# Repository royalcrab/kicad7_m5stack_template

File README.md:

# KiCad7-M5Stack-Template for KiCad7

- [Original](https://github.com/botanicfields/KiCad-Template-M5Stack)

A PCB template of modules of M5Stack with footprints for KiCad.
This is a modified version for KiCad7.

## for KiCad 6
https://github.com/botanicfields/KiCad6-Environment

## for KiCad 5
- Manufacture with a thickness of 1.0 mm.
- M-BUS pin numbers match pin headers and pin sockets in the KiCad library.
- The template has a notch, but it may be actually needed only for the M5Stack controller board.

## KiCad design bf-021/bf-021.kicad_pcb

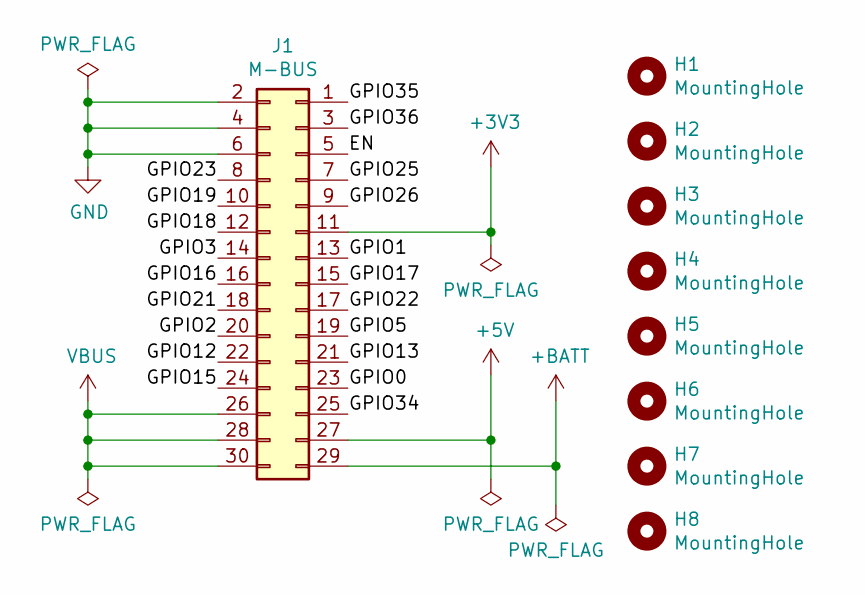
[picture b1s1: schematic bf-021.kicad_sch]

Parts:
H1, H2, H3, H4: MountingHole; BF@MountingHole_3.2mm_M3
H5, H6, H7, H8: MountingHole; BF@MountingHole_2.2mm_M2
J1: M-BUS; BF@M5Stack_MBUS

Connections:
+3V3: J1.11
+5V: J1.27
+BATT: J1.29
/EN: J1.5
/GPIO0: J1.23
/GPIO1: J1.13
/GPIO2: J1.20
/GPIO3: J1.14
/GPIO5: J1.19
/GPIO12: J1.22
/GPIO13: J1.21
/GPIO15: J1.24
/GPIO16: J1.16
/GPIO17: J1.15
/GPIO18: J1.12
/GPIO19: J1.10
/GPIO21: J1.18
/GPIO22: J1.17
/GPIO23: J1.8
/GPIO25: J1.7
/GPIO26: J1.9
/GPIO34: J1.25
/GPIO35: J1.1
/GPIO36: J1.3
GND: J1.2, J1.4, J1.6
VBUS: J1.26, J1.28, J1.30

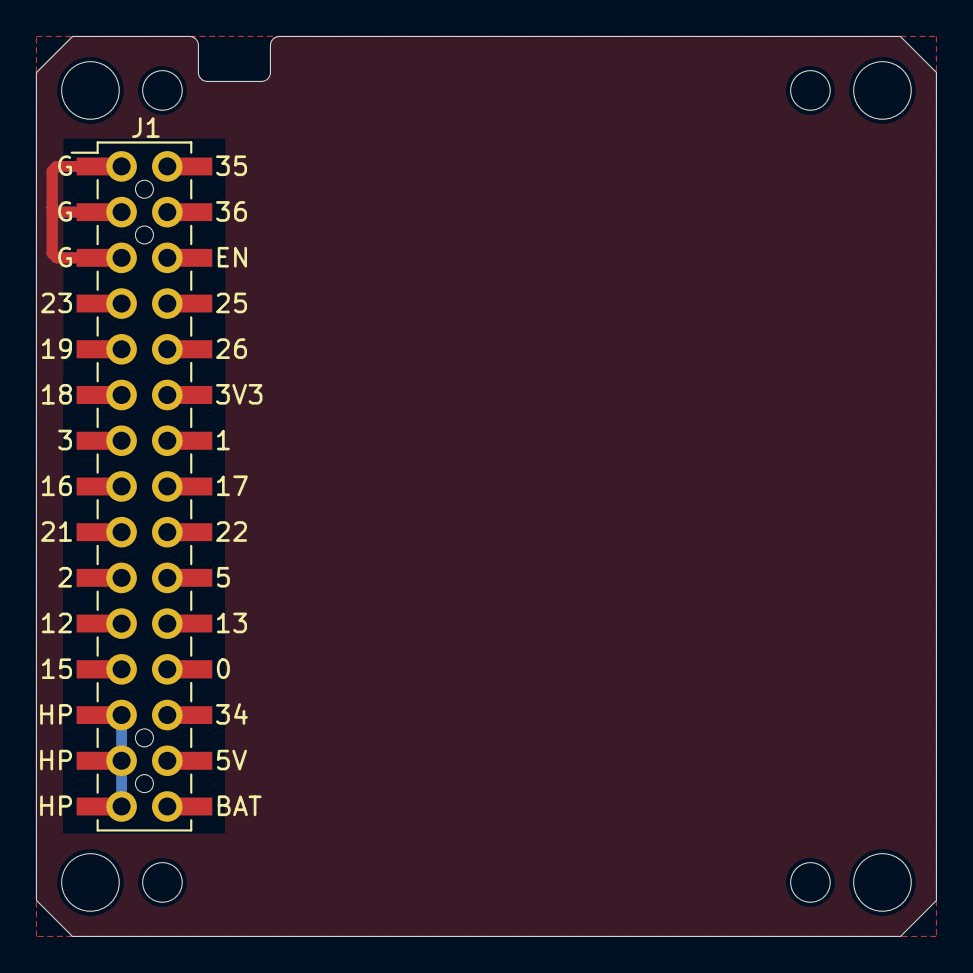
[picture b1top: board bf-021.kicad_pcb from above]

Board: 2 copper layers, 50.0 x 50.0 mm, 9 parts (0 on the bottom side), 2 nets.

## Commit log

2024-01-14 first

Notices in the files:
bf-021/bf-021.kicad_pcb:
Copyright 2022 BotanicFields, Inc.
